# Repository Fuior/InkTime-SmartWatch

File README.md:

# InkTime-SmartWatch

## Project Overview

InkTime-SmartWatch is a compact wearable embedded system built around the Nordic nRF52840 microcontroller, designed for ultra-low-power smartwatch applications using an e-paper display, motion sensing, haptic feedback, battery monitoring and USB-C charging.

The project integrates power management, sensing, display driving and wireless communication into a compact PCB optimized for enclosure integration.

---

# Block Diagram

```text
USB-C Input
   ↓
LiPo Charger
   ↓
LiPo Battery
   ↓
DC/DC Converter
   ↓
nRF52840 MCU
 ├── E-Paper Display (SPI)
 ├── IMU Sensor (I2C)
 ├── Fuel Gauge (I2C)
 ├── Haptic Driver (I2C / GPIO)
 ├── Buttons (GPIO Interrupts)
 ├── SWD Debug Interface
 └── BLE Antenna
```

---

# Bill of Materials (BOM)

| Component         | Part             | Function                       |
| ----------------- | ---------------- | ------------------------------ |
| MCU               | nRF52840-QFAA    | Main microcontroller           |
| Battery Charger   | BQ25180          | LiPo charging                  |
| DC/DC Converter   | RT6150           | Voltage regulation             |
| IMU               | Motion sensor    | Accelerometer / motion sensing |
| Fuel Gauge        | MAX17048         | Battery level measurement      |
| Haptic Driver     | DRV2605          | Vibration motor control        |
| Display Connector | 24-pin FPC       | E-paper connection             |
| USB-C Connector   | Type-C           | Charging and power             |
| ESD Protection    | USBLC6           | USB protection                 |
| Buttons           | Tactile switches | User input                     |
| SWD Header        | TC2030           | Programming/debug              |

---

# Hardware Functional Description

## Microcontroller Core

The central processing unit of the smartwatch is the Nordic nRF52840, a BLE-enabled ARM Cortex-M4 microcontroller selected for:

* low power consumption
* integrated Bluetooth Low Energy
* SPI / I2C / GPIO flexibility
* wearable device suitability

The MCU handles:

* display updates
* sensor acquisition
* battery monitoring
* haptic events
* user input

---

## Power Management

The power subsystem contains:

### LiPo Charger

BQ25180 charger manages battery charging through USB-C input.

Functions:

* battery charging
* input protection
* charging regulation

### DC/DC Converter

RT6150 converts battery voltage to regulated supply rails for MCU and peripherals.

Main outputs:

* 3.3V logic supply
* regulated peripheral rail

---

## Display Subsystem

The smartwatch uses an e-paper display interface.

Advantages:

* ultra low power
* persistent image retention
* sunlight readability

Dedicated E-Paper Driver section generates required voltages.

---

## IMU Sensor

The inertial measurement unit provides motion data:

* acceleration
* movement detection
* orientation sensing

Used for:

* wake-up events
* motion-based interface control

---

## Fuel Gauge

MAX17048 continuously measures battery charge state.

Functions:

* battery voltage monitoring
* charge estimation
* low battery alert

---

## Haptic Feedback

DRV2605 driver controls the vibration motor.

Allows:

* notifications
* tactile feedback
* programmable vibration patterns

---

## USB-C Interface

USB-C connector provides:

* charging input
* power delivery
* ESD protected connection

Protection implemented using USBLC6 device.

---

## Buttons

Three hardware buttons are implemented:

* SW_UP
* SW_INT
* SW_DN

Used for:

* navigation
* selection
* wake-up interrupt

---

# nRF52840 Pin Assignment

| nRF52840 Pin | Connected Module | Interface | Purpose       |
| ------------ | ---------------- | --------- | ------------- |
| P0.13        | Display Clock    | SPI       | Display clock |
| P0.15        | Display Data     | SPI       | Display data  |
| P0.24        | Haptic control   | GPIO      | Motor trigger |
| P0.26        | IMU SDA          | I2C       | Sensor data   |
| P0.27        | IMU SCL          | I2C       | Sensor clock  |
| P1.xx        | Buttons          | GPIO      | User input    |
| SWDIO        | Debug            | SWD       | Programming   |
| SWDCLK       | Debug            | SWD       | Programming   |

---

# Power Consumption Considerations

Estimated current consumption:

* MCU active: ~5 mA
* E-paper refresh: ~20 mA
* IMU active: ~1 mA
* Haptic pulse: ~80 mA

Battery sizing selected for wearable operation with optimized duty cycle.

---

# Mechanical Integration

The mechanical assembly contains:

* PCB
* LiPo battery
* e-paper display
* vibration motor
* enclosure

Placement order:

top to bottom:

Display → Battery → PCB → Case

---

# Design Decisions

Main design goals:

* compact PCB layout
* low power architecture
* short SPI lines to display
* antenna edge placement
* battery direct pad connection

---

# Rendered Images

Project folder contains:

* PCB 3D top render
* PCB 3D side render
* complete assembly top render
* complete assembly side render
* exploded mechanical view

---

# Files Included

## Hardware

* schematic (.sch)
* board (.brd)
* schematic PDF

## Manufacturing

* gerbers.zip
* BOM
* CPL

## Mechanical

* STEP exploded assembly
* STEP PCB 3D
* Fusion360 project

## Images

* PCB renders
* assembly renders

---

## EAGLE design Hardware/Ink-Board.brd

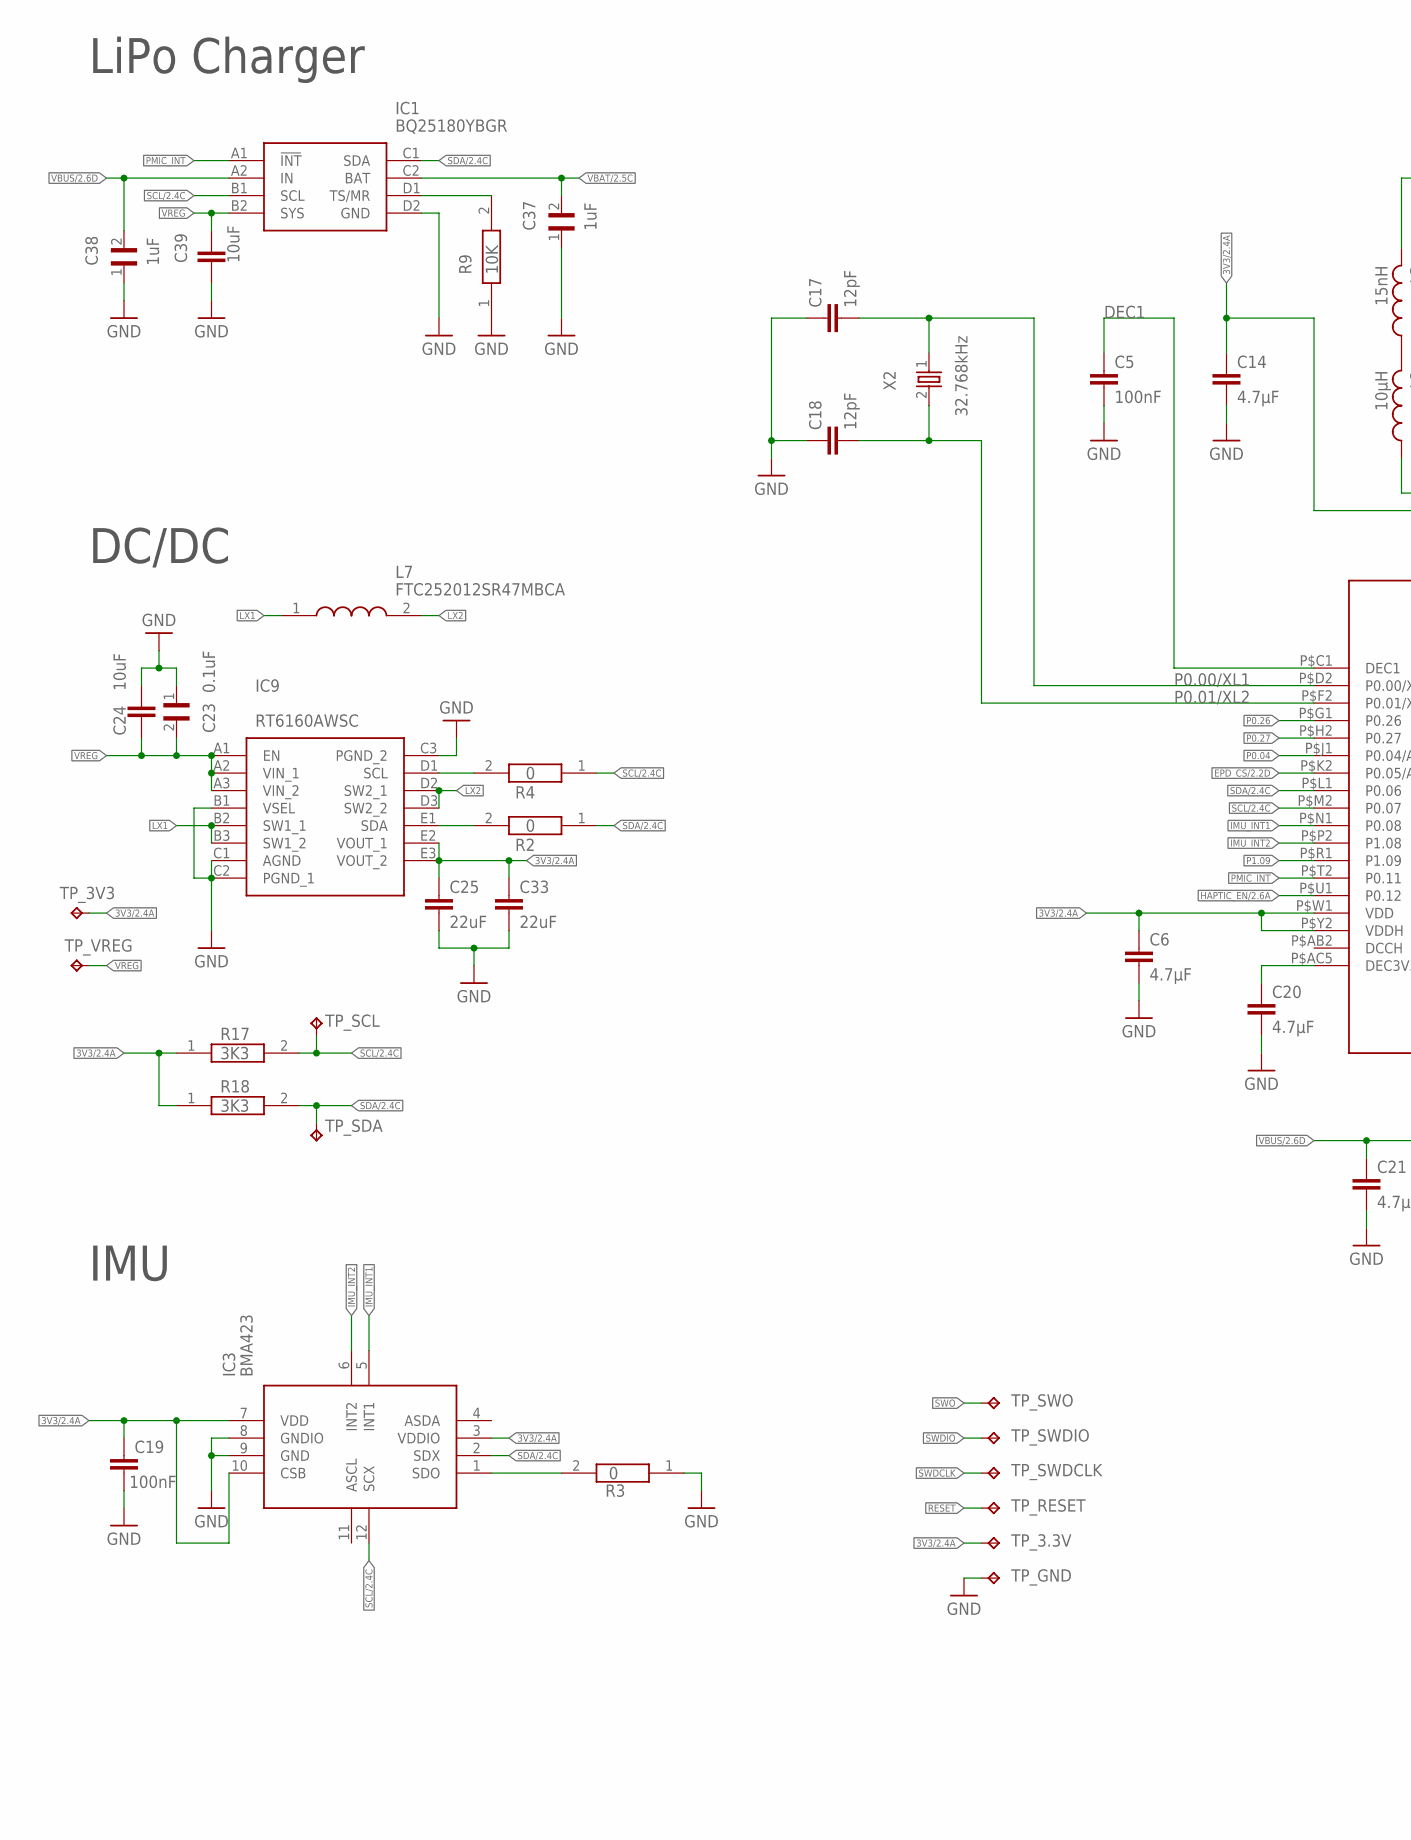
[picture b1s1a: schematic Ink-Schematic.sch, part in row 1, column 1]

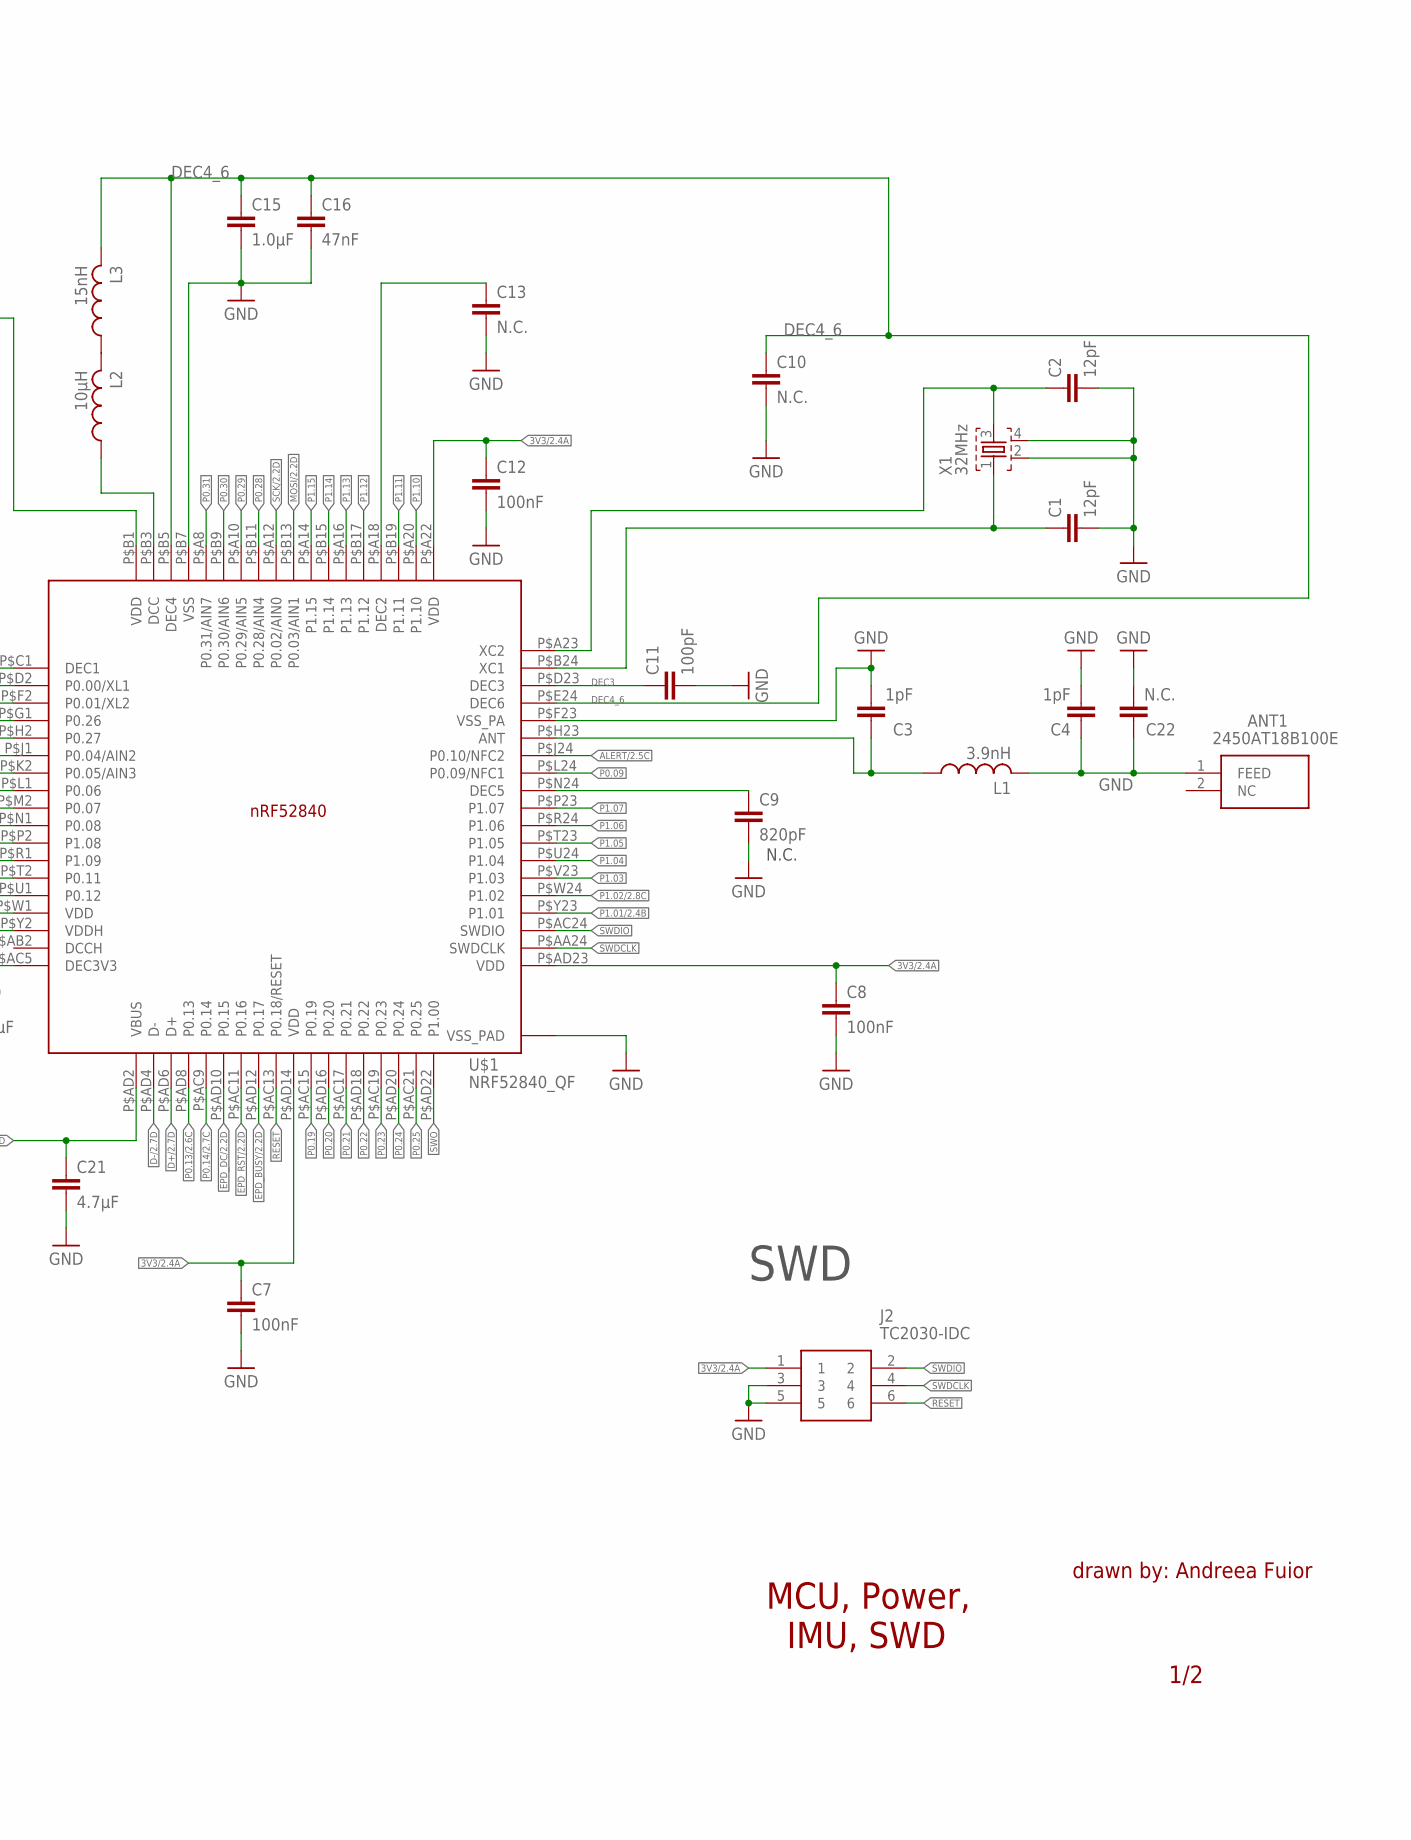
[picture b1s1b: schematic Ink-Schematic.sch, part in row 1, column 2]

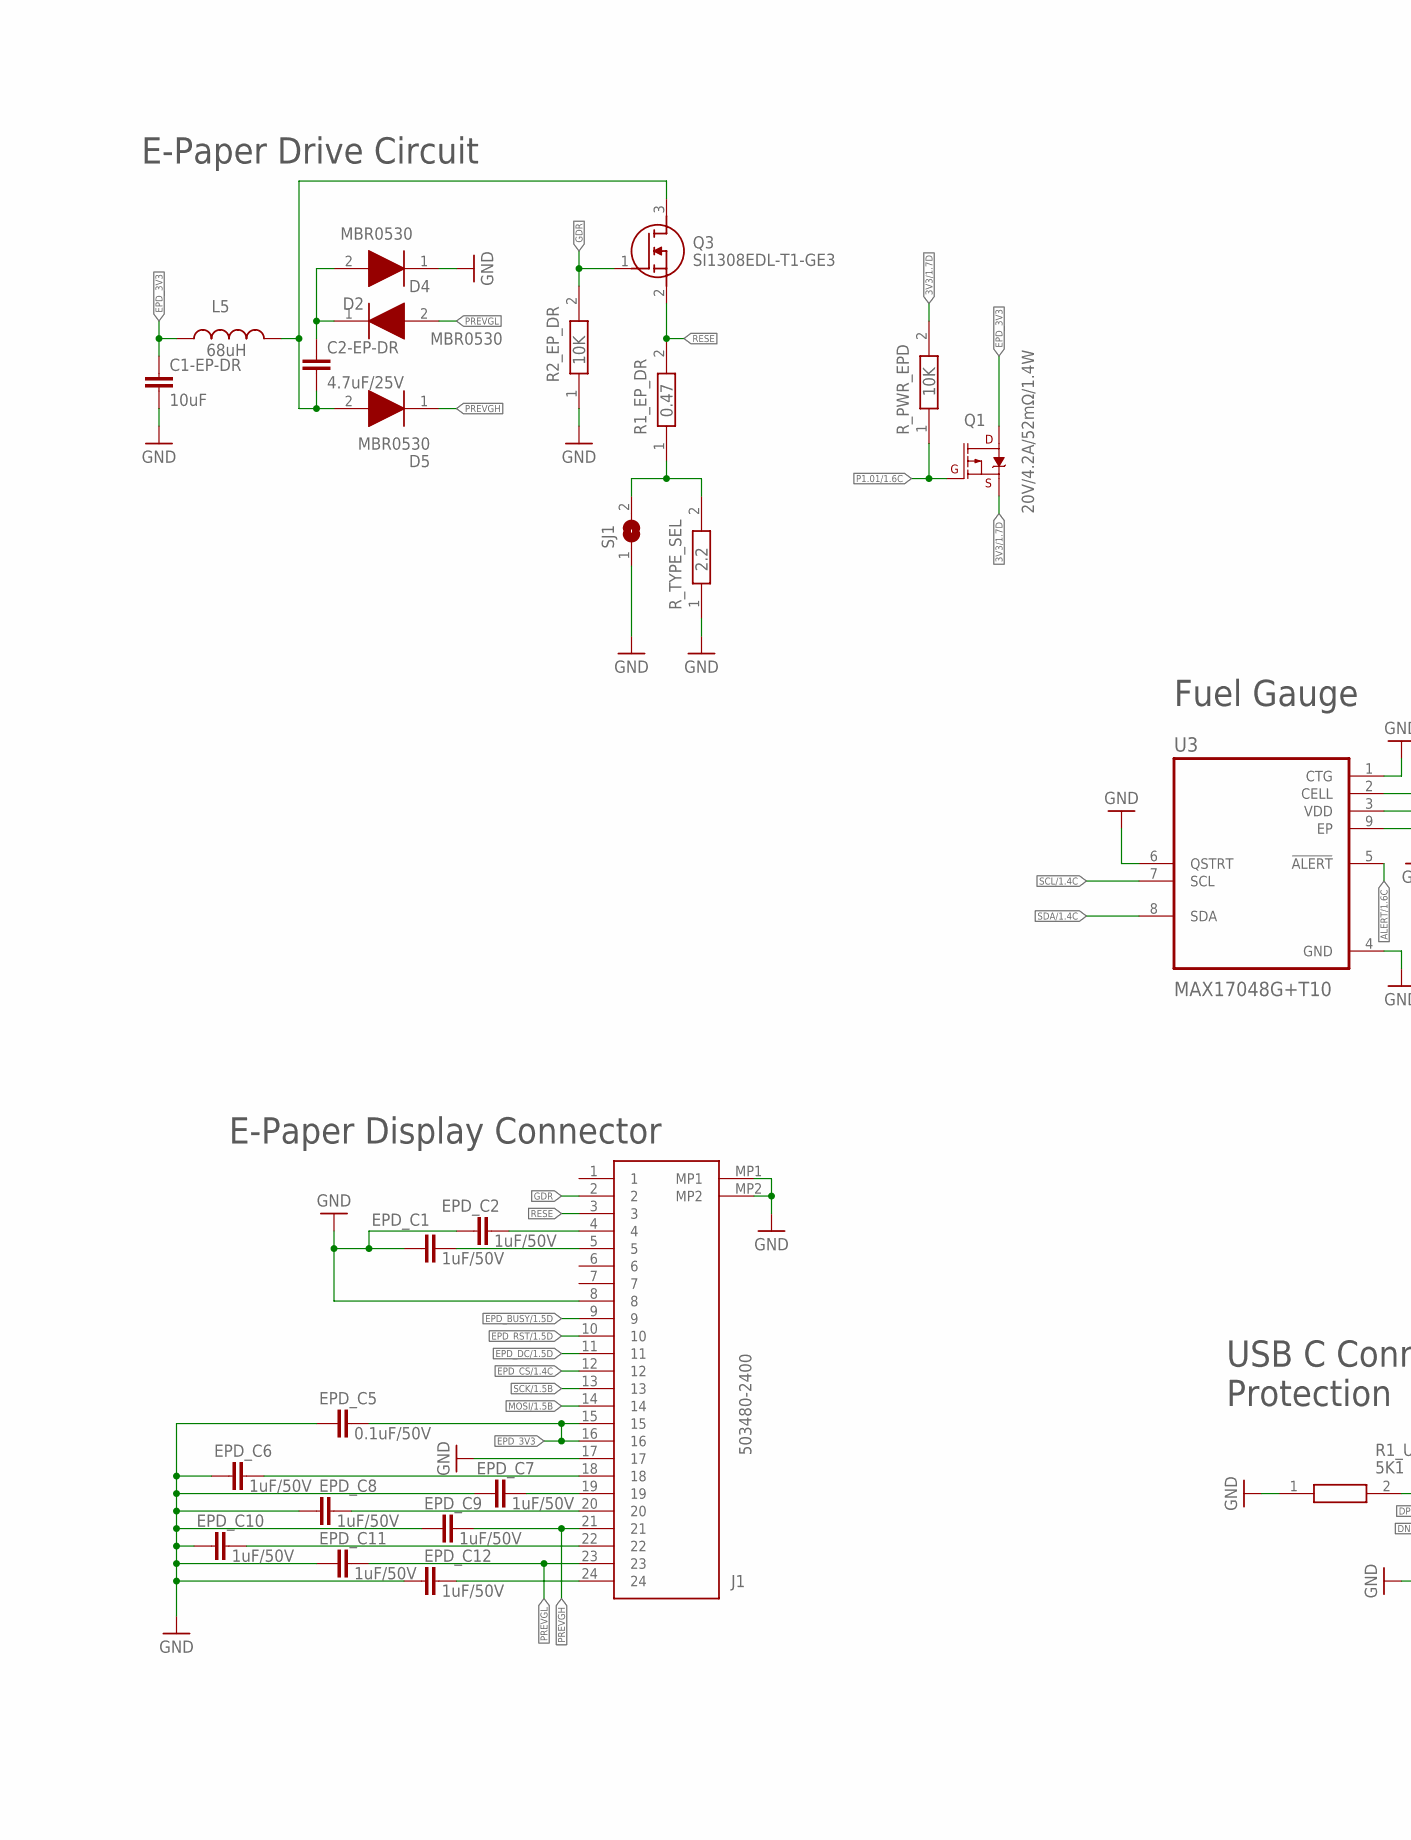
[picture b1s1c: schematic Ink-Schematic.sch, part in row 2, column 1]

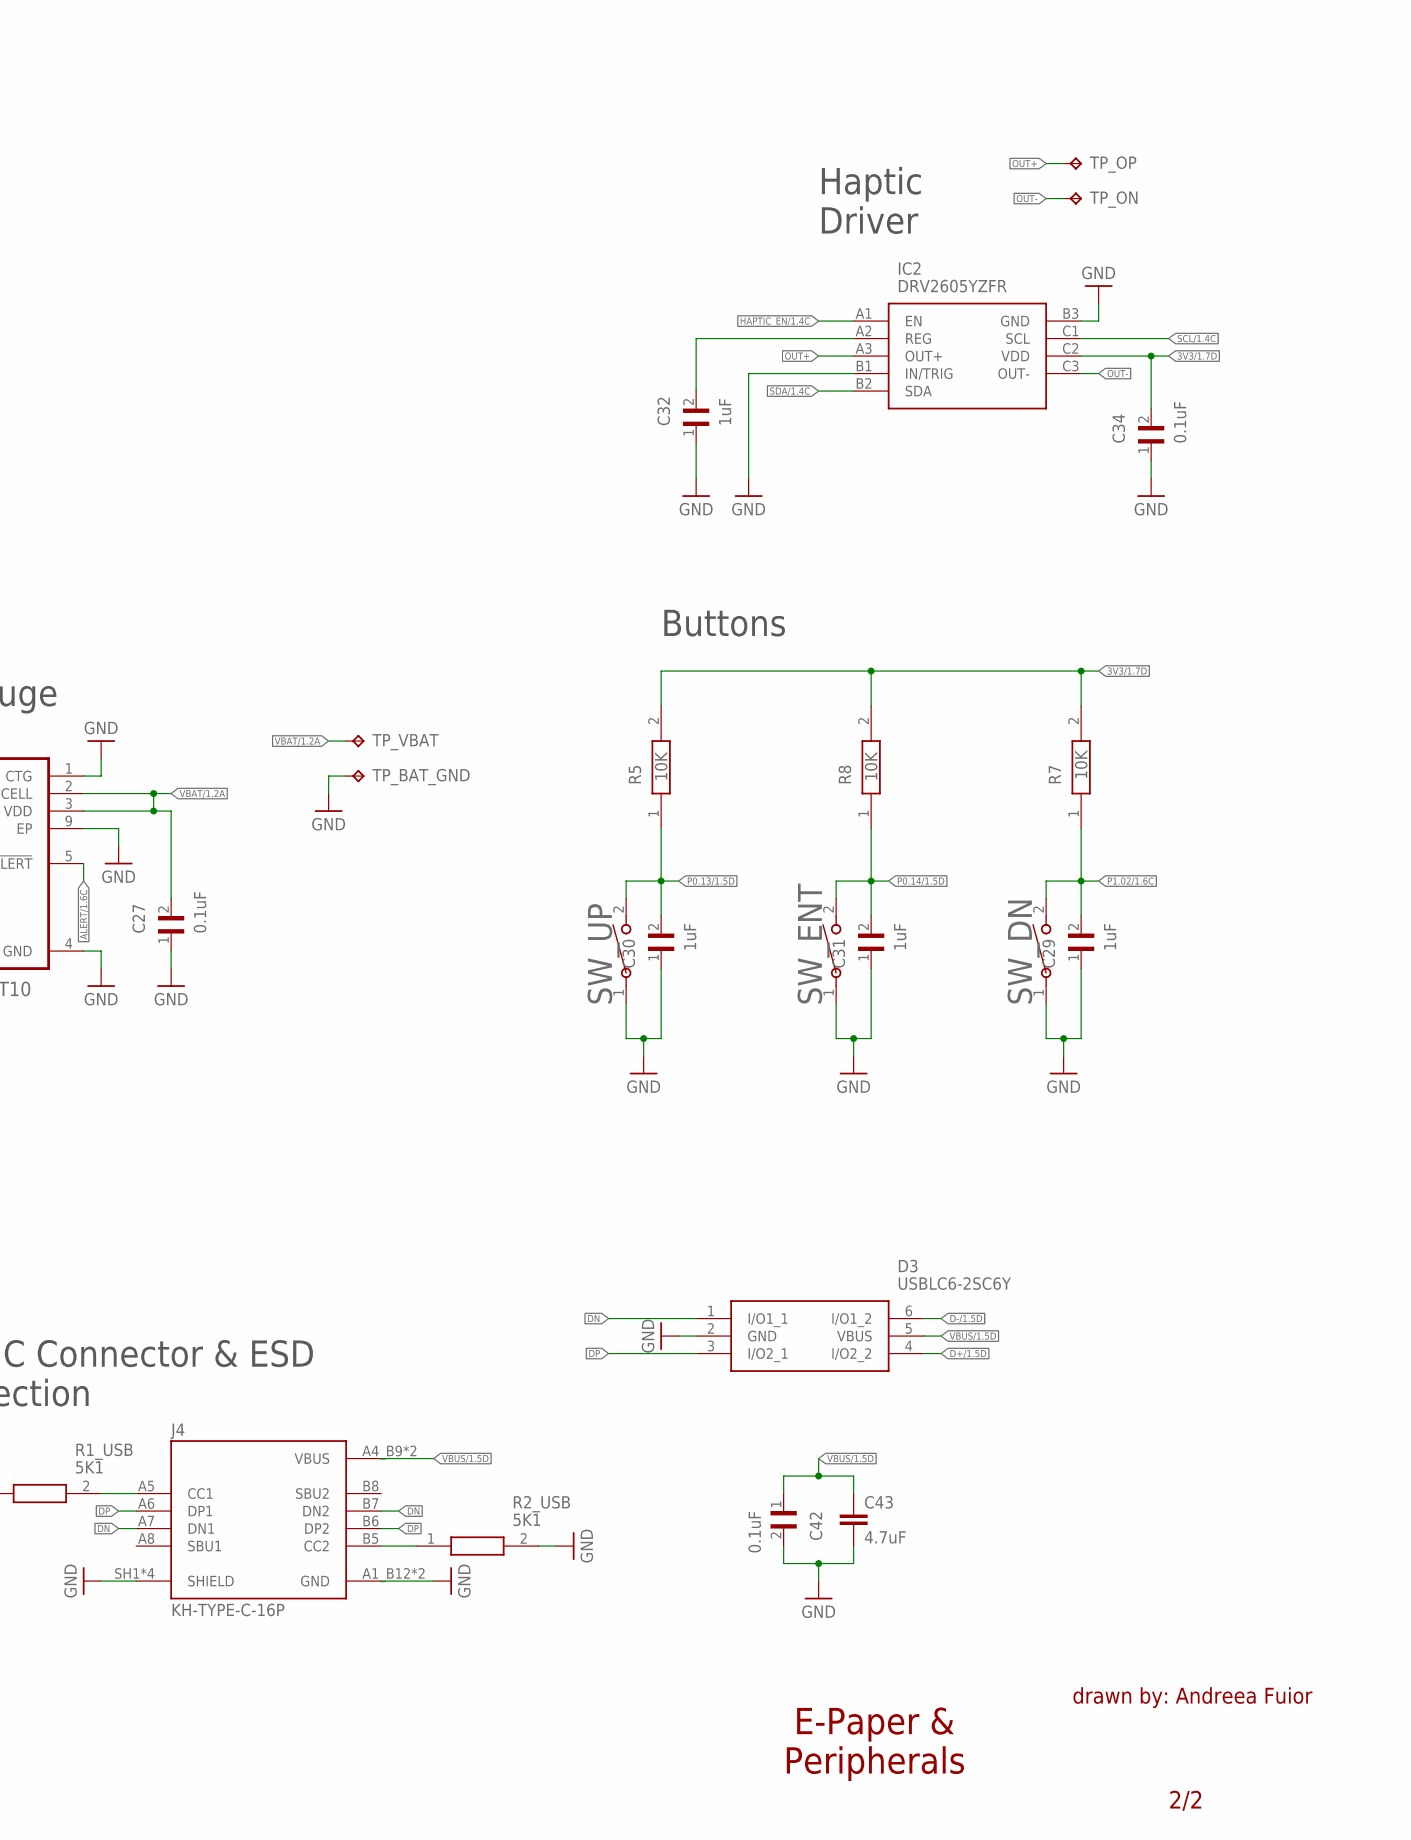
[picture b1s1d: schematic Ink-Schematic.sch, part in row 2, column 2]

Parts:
ANT1: 2450AT18B100E; 2450AT18B100E_ANTC3216X140N
C1, C2, C17, C18: 12pF; NORDIC_NRF_3_RESC0201_L
C1-EP-DR, C24, C39: 10uF; NORDIC_NRF_3_RESC0402_L
C2-EP-DR: 4.7uF/25V; NORDIC_NRF_3_RESC0402_L
C3, C4: 1pF; NORDIC_NRF_3_RESC0201_L
C5, C7, C8, C12, C19: 100nF; NORDIC_NRF_3_RESC0201_L
C6, C14, C20, C21: 4.7μF; NORDIC_NRF_3_RESC0402_L
C9: 820pF; NORDIC_NRF_3_RESC0201_L
C10, C13, C22: N.C.; NORDIC_NRF_3_RESC0201_L
C11: 100pF; NORDIC_NRF_3_RESC0201_L
C15: 1.0μF; NORDIC_NRF_3_RESC0402_L
C16: 47nF; NORDIC_NRF_3_RESC0201_L
C23, C27, C34, C42: 0.1uF; GRM011R60J152KE01L_2_CAPC0201X13N
C25, C33: 22uF; NORDIC_NRF_3_RESC0402_L
C29, C30, C31, C32, C37, C38: 1uF; GRM011R60J152KE01L_2_CAPC0201X13N
C43: 4.7uF; NORDIC_NRF_3_RESC0402_L
D2, D4, D5: MBR0530; ESP32_C6_LIBRARY_5_SOD3716X135N
D3: USBLC6-2SC6Y; ESP32_C6_LIBRARY_3_SOT95P280X145-6N
EPD_C1, EPD_C2, EPD_C6, EPD_C7, EPD_C8, EPD_C9, EPD_C10, EPD_C11, EPD_C12: 1uF/50V; NORDIC_NRF_3_RESC0402_L
EPD_C5: 0.1uF/50V; NORDIC_NRF_3_RESC0402_L
IC1: BQ25180YBGR; BQ25180YBGR_BGA8C40P2X4_100X155X50
IC2: DRV2605YZFR; DRV2605YZFR_BGA9C50P3X3_144X144X62
IC3: BMA423; BMA423_BMA423
IC9: RT6160AWSC; RT6160AWSC_BGA15C40P3X5_140X230X60
J1: 503480-2400; 503480-2400_5034802400
J2: TC2030-IDC; TC2030-IDC_TC2030IDC
J4: KH-TYPE-C-16P; KH-TYPE-C-16P_KINGHELM_KH-TYPE-C-16P
L1: 3.9nH; NORDIC_NRF_2_RESC0402_L
L2: 10μH; NORDIC_NRF_2_RESC0402_L
L3: 15nH; NORDIC_NRF_2_RESC0402_L
L5: 68uH; NORDIC_NRF_2_RESC0402_L
L7: FTC252012SR47MBCA; MLP2016SR47MT0S1_INDC2016X100N
Q1: 20V/4.2A/52mΩ/1.4W; ESP32_C6_LIBRARY_4_ESP32_C6_LIBRARY_4_ESP32_C6_LIBRARY_4_ES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
Q3: SI1308EDL-T1-GE3; ESP32_C6_LIBRARY_6_SOT65P210X110-3N
R1_EP_DR: 0.47; CPF0201D7K68C1_0201
R1_USB, R2_USB: 5K1; CPF0201D7K68C1_0201
R2, R3, R4: 0; CPF0201D7K68C1_0201
R2_EP_DR, R5, R7, R8, R9: 10K; CPF0201D7K68C1_0201
R17, R18: 3K3; CPF0201D7K68C1_0201
R_PWR_EPD: 10K; CPF0201D7K68C1_0201
R_TYPE_SEL: 2.2; CPF0201D7K68C1_0201
SJ1: ESP32_C6_LIBRARY_7_JUMPER_SJ
SW_DN: 2025-10-22_07-23-44_LIBRARY_EVP-AKE31ASW_EVP-AKE3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; 2025-10-22_07-23-44_LIBRARY_SW_EVP-AKE31A_PAN
SW_ENT: 2025-10-22_07-23-44_LIBRARY_EVP-AKE31ASW_EVP-AKE3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; 2025-10-22_07-23-44_LIBRARY_SW_EVP-AKE31A_PAN
SW_UP: 2025-10-22_07-23-44_LIBRARY_EVP-AKE31ASW_EVP-AKE3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; 2025-10-22_07-23-44_LIBRARY_SW_EVP-AKE31A_PAN
TP_3.3V, TP_3V3: HECTOR_WATCH_1_TPTP20R; HECTOR_WATCH_1_TP20R
TP_BAT_GND: HECTOR_WATCH_1_TPTP20R; HECTOR_WATCH_1_TP20R
TP_GND: HECTOR_WATCH_1_TPTP20R; HECTOR_WATCH_1_TP20R
TP_ON: HECTOR_WATCH_1_TPTP20R; HECTOR_WATCH_1_TP20R
TP_OP: HECTOR_WATCH_1_TPTP20R; HECTOR_WATCH_1_TP20R
TP_RESET: HECTOR_WATCH_1_TPTP20R; HECTOR_WATCH_1_TP20R
TP_SCL: HECTOR_WATCH_1_TPTP20R; HECTOR_WATCH_1_TP20R
TP_SDA: HECTOR_WATCH_1_TPTP20R; HECTOR_WATCH_1_TP20R
TP_SWDCLK: HECTOR_WATCH_1_TPTP20R; HECTOR_WATCH_1_TP20R
TP_SWDIO: HECTOR_WATCH_1_TPTP20R; HECTOR_WATCH_1_TP20R
TP_SWO: HECTOR_WATCH_1_TPTP20R; HECTOR_WATCH_1_TP20R
TP_VBAT: HECTOR_WATCH_1_TPTP20R; HECTOR_WATCH_1_TP20R
TP_VREG: HECTOR_WATCH_1_TPTP20R; HECTOR_WATCH_1_TP20R
U3: MAX17048G+T10; ESP32_C6_LIBRARY_SON50P200X200X80-9N
U$1: NRF52840_QF; NORDIC_NRF_4_AQFN50P700X700X85_HS-74N
X1: 32MHz; NORDIC_NRF_BT-XTAL_2016_N
X2: 32.768kHz; NORDIC_NRF_1_XTAL_3215_N

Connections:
3V3/1.7D: C34.2, IC2.C2 (VDD), Q1.2 (S), R5.2, R7.2, R8.2, R_PWR_EPD.2
3V3/2.4A: C6.1, C7.1, C8.1, C12.1, C14.1, C19.1, C25.1, C33.1, IC3.3 (VDDIO), IC3.7 (VDD), IC3.10 (CSB), IC9.E2 (VOUT_1), IC9.E3 (VOUT_2), J2.1, R17.1, R18.1, TP_3.3V.TP, TP_3V3.TP, U$1.P$A22 (VDD), U$1.P$AD14 (VDD), U$1.P$AD23 (VDD), U$1.P$B1 (VDD), U$1.P$W1 (VDD), U$1.P$Y2 (VDDH)
ALERT/1.6C: U3.5 (!ALERT)
ALERT/2.5C: U$1.P$J24 (P0.10/NFC2)
D+/1.5D: D3.4 (I/O2_2)
D+/2.7D: U$1.P$AD6 (D+)
D-/1.5D: D3.6 (I/O1_2)
D-/2.7D: U$1.P$AD4 (D-)
DEC1: C5.1, U$1.P$C1 (DEC1)
DEC3: C11.1, U$1.P$D23 (DEC3)
DEC4_6: C10.1, C15.1, C16.1, L3.2, U$1.P$B5 (DEC4), U$1.P$E24 (DEC6)
DN: D3.1 (I/O1_1), J4.A7 (DN1), J4.B7 (DN2)
DP: D3.3 (I/O2_1), J4.A6 (DP1), J4.B6 (DP2)
EPD_3V3: C1-EP-DR.1, EPD_C5.1, J1.15, J1.16, L5.1, Q1.3 (D)
EPD_BUSY/1.5D: J1.9
EPD_BUSY/2.2D: U$1.P$AD12 (P0.17)
EPD_CS/1.4C: J1.12
EPD_CS/2.2D: U$1.P$K2 (P0.05/AIN3)
EPD_DC/1.5D: J1.11
EPD_DC/2.2D: U$1.P$AD10 (P0.15)
EPD_RST/1.5D: J1.10
EPD_RST/2.2D: U$1.P$AC11 (P0.16)
GDR: J1.2, Q3.1 (G), R2_EP_DR.2
GND: ANT1.1 (FEED), C1.2, C1-EP-DR.2, C2.2, C3.2, C4.1, C4.2, C5.2, C6.2, C7.2, C8.2, C9.2, C10.2, C11.2, C12.2, C13.2, C14.2, C15.2, C16.2, C17.1, C18.1, C19.2, C20.2, C21.2, C22.1, C22.2, C23.1, C24.2, C25.2, C27.1, C29.1, C30.1, C31.1, C32.1, C33.2, C34.1, C37.1, C38.1, C39.2, C42.2, C43.2, D3.2 (GND), D4.1 (K), EPD_C1.2, EPD_C2.2, EPD_C5.2, EPD_C6.2, EPD_C7.2, EPD_C8.2, EPD_C9.2, EPD_C10.2, EPD_C11.2, EPD_C12.2, IC1.D2 (GND), IC2.B1 (IN/TRIG), IC2.B3 (GND), IC3.8 (GNDIO), IC3.9 (GND), IC9.B1 (VSEL), IC9.C1 (AGND), IC9.C2 (PGND_1), IC9.C3 (PGND_2), J1.8, J1.17, J1.MP1, J1.MP2, J2.3, J2.5, J4.A1_B12 (GND), J4.A12_B1 (GND), J4.SH1 (SHIELD), J4.SH2 (SHIELD), J4.SH3 (SHIELD), J4.SH4 (SHIELD), L1.2, R1_USB.1, R2_EP_DR.1, R2_USB.2, R3.1, R9.1, R_TYPE_SEL.1, SJ1.1, SW_DN.1, SW_ENT.1, SW_UP.1, TP_BAT_GND.TP, TP_GND.TP, U3.1 (CTG), U3.4 (GND), U3.6 (QSTRT), U3.9 (EP), U$1.P$74 (VSS_PAD), U$1.P$75 (VSS_PAD), U$1.P$76 (VSS_PAD), U$1.P$77 (VSS_PAD), U$1.P$78 (VSS_PAD), U$1.P$79 (VSS_PAD), U$1.P$80 (VSS_PAD), U$1.P$81 (VSS_PAD), U$1.P$82 (VSS_PAD), U$1.P$83 (VSS_PAD), U$1.P$84 (VSS_PAD), U$1.P$85 (VSS_PAD), U$1.P$86 (VSS_PAD), U$1.P$87 (VSS_PAD), U$1.P$88 (VSS_PAD), U$1.P$89 (VSS_PAD), U$1.P$90 (VSS_PAD), U$1.P$B7 (VSS), U$1.P$F23 (VSS_PA), X1.2, X1.4
HAPTIC_EN/1.4C: IC2.A1 (EN)
HAPTIC_EN/2.6A: U$1.P$U1 (P0.12)
IMU_INT1: IC3.5 (INT1), U$1.P$N1 (P0.08)
IMU_INT2: IC3.6 (INT2), U$1.P$P2 (P1.08)
LX1: IC9.B2 (SW1_1), IC9.B3 (SW1_2), L7.1
LX2: IC9.D2 (SW2_1), IC9.D3 (SW2_2), L7.2
MOSI/1.5B: J1.14
MOSI/2.2D: U$1.P$B13 (P0.03/AIN1)
unnamed: C9.1, U$1.P$N24 (DEC5)
unnamed: C3.1, L1.1, U$1.P$H23 (ANT)
unnamed: C1.1, U$1.P$B24 (XC1), X1.1
unnamed: C2.1, U$1.P$A23 (XC2), X1.3
unnamed: C13.1, U$1.P$A18 (DEC2)
unnamed: L2.1, U$1.P$B3 (DCC)
unnamed: L2.2, L3.1
unnamed: C20.1, U$1.P$AC5 (DEC3V3)
unnamed: C2-EP-DR.2, D5.2 (A), L5.2, Q3.3 (D)
unnamed: IC9.D1 (SCL), R4.2
unnamed: IC1.D1 (TS/MR), R9.2
unnamed: C2-EP-DR.1, D2.1 (K), D4.2 (A)
unnamed: IC9.E1 (SDA), R2.2
unnamed: EPD_C2.1, J1.4
unnamed: R1_EP_DR.1, R_TYPE_SEL.2, SJ1.2
unnamed: IC3.1 (SDO), R3.2
unnamed: EPD_C6.1, J1.18
unnamed: EPD_C7.1, J1.19
unnamed: EPD_C8.1, J1.20
unnamed: EPD_C1.1, J1.5
unnamed: EPD_C10.1, J1.22
unnamed: EPD_C12.1, J1.24
unnamed: C32.2, IC2.A2 (REG)
unnamed: J4.B5 (CC2), R2_USB.1
unnamed: J4.A5 (CC1), R1_USB.2
OUT+: IC2.A3 (OUT+), TP_OP.TP
OUT-: IC2.C3 (OUT-), TP_ON.TP
P0.00/XL1: C17.2, U$1.P$D2 (P0.00/XL1), X2.1
P0.01/XL2: C18.2, U$1.P$F2 (P0.01/XL2), X2.2
P0.04: U$1.P$J1 (P0.04/AIN2)
P0.09: U$1.P$L24 (P0.09/NFC1)
P0.13/1.5D: C30.2, R5.1, SW_UP.2
P0.13/2.6C: U$1.P$AD8 (P0.13)
P0.14/1.5D: C31.2, R8.1, SW_ENT.2
P0.14/2.7C: U$1.P$AC9 (P0.14)
P0.19: U$1.P$AC15 (P0.19)
P0.20: U$1.P$AD16 (P0.20)
P0.21: U$1.P$AC17 (P0.21)
P0.22: U$1.P$AD18 (P0.22)
P0.23: U$1.P$AC19 (P0.23)
P0.24: U$1.P$AD20 (P0.24)
P0.25: U$1.P$AC21 (P0.25)
P0.26: U$1.P$G1 (P0.26)
P0.27: U$1.P$H2 (P0.27)
P0.28: U$1.P$B11 (P0.28/AIN4)
P0.29: U$1.P$A10 (P0.29/AIN5)
P0.30: U$1.P$B9 (P0.30/AIN6)
P0.31: U$1.P$A8 (P0.31/AIN7)
P1.01/1.6C: Q1.1 (G), R_PWR_EPD.1
P1.01/2.4B: U$1.P$Y23 (P1.01)
P1.02/1.6C: C29.2, R7.1, SW_DN.2
P1.02/2.8C: U$1.P$W24 (P1.02)
P1.03: U$1.P$V23 (P1.03)
P1.04: U$1.P$U24 (P1.04)
P1.05: U$1.P$T23 (P1.05)
P1.06: U$1.P$R24 (P1.06)
P1.07: U$1.P$P23 (P1.07)
P1.09: U$1.P$R1 (P1.09)
P1.10: U$1.P$A20 (P1.10)
P1.11: U$1.P$B19 (P1.11)
P1.12: U$1.P$B17 (P1.12)
P1.13: U$1.P$A16 (P1.13)
P1.14: U$1.P$B15 (P1.14)
P1.15: U$1.P$A14 (P1.15)
PMIC_INT: IC1.A1 (!INT), U$1.P$T2 (P0.11)
PREVGH: D5.1 (K), EPD_C9.1, J1.21
PREVGL: D2.2 (A), EPD_C11.1, J1.23
RESE: J1.3, Q3.2 (S), R1_EP_DR.2
RESET: J2.6, TP_RESET.TP, U$1.P$AC13 (P0.18/RESET)
SCK/1.5B: J1.13
SCK/2.2D: U$1.P$A12 (P0.02/AIN0)
SCL/1.4C: IC2.C1 (SCL), U3.7 (SCL)
SCL/2.4C: IC1.B1 (SCL), IC3.12 (SCX), R4.1, R17.2, TP_SCL.TP, U$1.P$M2 (P0.07)
SDA/1.4C: IC2.B2 (SDA), U3.8 (SDA)
SDA/2.4C: IC1.C1 (SDA), IC3.2 (SDX), R2.1, R18.2, TP_SDA.TP, U$1.P$L1 (P0.06)
SWDCLK: J2.4, TP_SWDCLK.TP, U$1.P$AA24 (SWDCLK)
SWDIO: J2.2, TP_SWDIO.TP, U$1.P$AC24 (SWDIO)
SWO: TP_SWO.TP, U$1.P$AD22 (P1.00)
VBAT/1.2A: C27.2, TP_VBAT.TP, U3.2 (CELL), U3.3 (VDD)
VBAT/2.5C: C37.2, IC1.C2 (BAT)
VBUS/1.5D: C42.1, C43.1, D3.5 (VBUS), J4.A4_B9 (VBUS), J4.A9_B4 (VBUS)
VBUS/2.6D: C21.1, C38.2, IC1.A2 (IN), U$1.P$AD2 (VBUS)
VREG: C23.2, C24.1, C39.1, IC1.B2 (SYS), IC9.A1 (EN), IC9.A2 (VIN_1), IC9.A3 (VIN_2), TP_VREG.TP

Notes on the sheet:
SWD
LiPo Charger
DC/DC
IMU
E-Paper Drive Circuit
E-Paper Display Connector
Haptic Driver
Buttons
Fuel Gauge
USB C Connector & ESD Protection
MCU, Power, IMU, SWD
drawn by: Andreea Fuior
E-Paper & Peripherals
1/2
2/2
N.C.

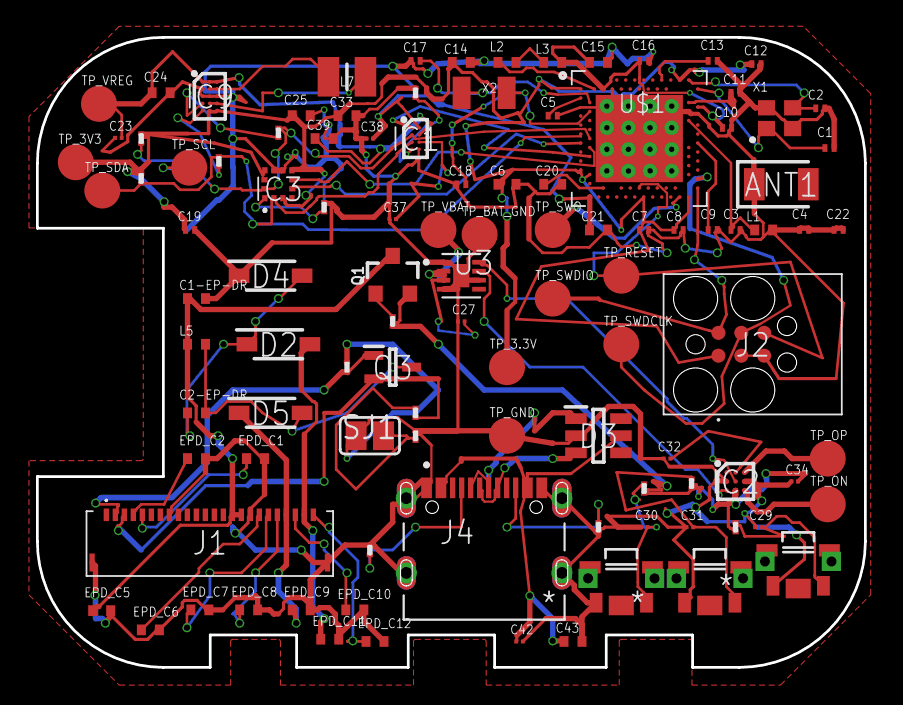
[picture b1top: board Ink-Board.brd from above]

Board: 2 copper layers, 46.0 x 35.0 mm, 105 parts (0 on the bottom side), 64 nets.

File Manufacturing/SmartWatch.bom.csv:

Reference Designators;Quantity;Description;Package;Value;Manufacturer;Manufacturer Part Number;Vendor;Vendor Part Number;Top/Bottom;
;1;Board;Board;;;;;;;
ANT1;1;Antennas 2.45GHz ANTENNA;2450AT18B100E_ANTC3216X140N;2450AT18B100E;;;;;Top;
C1, C2, C17, C18;4;Generic chip capacitor;NORDIC_NRF_3_RESC0201_L;12pF;;;;;Top;
C1-EP-DR, C24, C39;3;Generic chip capacitor;NORDIC_NRF_3_RESC0402_L;10uF;;;;;Top;
C2-EP-DR;1;Generic chip capacitor;NORDIC_NRF_3_RESC0402_L;4.7uF/25V;;;;;Top;
C3, C4;2;Generic chip capacitor;NORDIC_NRF_3_RESC0201_L;1pF;;;;;Top;
C5, C7, C8, C12, C19;5;Generic chip capacitor;NORDIC_NRF_3_RESC0201_L;100nF;;;;;Top;
C6, C14, C20, C21;4;Generic chip capacitor;NORDIC_NRF_3_RESC0402_L;4.7μF;;;;;Top;
C9;1;Generic chip capacitor;NORDIC_NRF_3_RESC0201_L;820pF;;;;;Top;
C10, C13, C22;3;Generic chip capacitor;NORDIC_NRF_3_RESC0201_L;N.C.;;;;;Top;
C11;1;Generic chip capacitor;NORDIC_NRF_3_RESC0201_L;100pF;;;;;Top;
C15;1;Generic chip capacitor;NORDIC_NRF_3_RESC0402_L;1.0μF;;;;;Top;
C16;1;Generic chip capacitor;NORDIC_NRF_3_RESC0201_L;47nF;;;;;Top;
C23, C27, C34, C42;4;Check availability;CAPC0201X13N;0.1uF;;;;;Top;
C25, C33;2;Generic chip capacitor;NORDIC_NRF_3_RESC0402_L;22uF;;;;;Top;
C29, C30, C31, C32, C37, C38;6;Check availability;CAPC0201X13N;1uF;;;;;Top;
C43;1;Generic chip capacitor;NORDIC_NRF_3_RESC0402_L;4.7uF;;;;;Top;
D2, D4, D5;3;ON SEMICONDUCTOR - MBR0530 - DIODE, SCHOTTKY, 0.5A, 30V, SOD-123;SOD3716X135N;MBR0530;;;;;Top;
D3;1;Low Cap. ESD Protection Auto SOT-23-6 STMicroelectronics USBLC6-2SC6Y, Dual Uni-Directional TVS Diode Array, 6-Pin SOT-23;SOT95P280X145-6N;USBLC6-2SC6Y;;;;;Top;
EPD_C1, EPD_C2, EPD_C6, EPD_C7, EPD_C8, EPD_C9, EPD_C10, EPD_C11, EPD_C12;9;Generic chip capacitor;NORDIC_NRF_3_RESC0402_L;1uF/50V;;;;;Top;
EPD_C5;1;Generic chip capacitor;NORDIC_NRF_3_RESC0402_L;0.1uF/50V;;;;;Top;
IC1;1;Charger IC Lithium Ion/Polymer, Lithium Iron Phosphate 8-DSBGA (1.6x1.1);BQ25180YBGR_BGA8C40P2X4_100X155X50;BQ25180YBGR;;;;;Top;
IC2;1;Haptic Driver for ERM/LRA with Built-In Library and Smart Loop Architecture;DRV2605YZFR_BGA9C50P3X3_144X144X62;DRV2605YZFR;;;;;Top;
IC3;1;Accelerometers Triaxial low-g 12bit Acceleration Sensor;BMA423_BMA423; BMA423;;;;;Top;
IC9;1;Buck-Boost Regulator Positive Output Step-Up/Step-Down I2C DC-DC Controller IC 15-WL-CSP (BSC) (1.4x2.3);RT6160AWSC_BGA15C40P3X5_140X230X60;RT6160AWSC;;;;;Top;
J1;1;FFC & FPC Connectors 0.5mm FPC RA SMT Dual Contact 24Ckt;503480-2400_5034802400;503480-2400;;;;;Top;
J2;1;CABLE ADAPTER 6 POS;TC2030-IDC_TC2030IDC;TC2030-IDC;;;;;Top;
J4;1;Check availability;KINGHELM_KH-TYPE-C-16P;KH-TYPE-C-16P;;;;;Top;
L1;1;Generic chip inductor;NORDIC_NRF_2_RESC0402_L;3.9nH;;;;;Top;
L2;1;Generic chip inductor;NORDIC_NRF_2_RESC0402_L; 10μH;;;;;Top;
L3;1;Generic chip inductor;NORDIC_NRF_2_RESC0402_L;15nH;;;;;Top;
L5;1;Generic chip inductor;NORDIC_NRF_2_RESC0402_L;68uH;;;;;Top;
L7;1;SMD / SMT Inductors (Coils), L=0.47?H, L x W x T :;MLP2016SR47MT0S1_INDC2016X100N;FTC252012SR47MBCA;;;;;Top;
Q1;1;P-channel MOSFETs;ESP32_WROVER_SPARKFUN-DISCRETESEMI_SOT23-3;20V/4.2A/52mΩ/1.4W;;;;;Top;
Q3;1;MOSFET N-Ch 30V 1.5A TrenchFET SC70 Vishay Si1308EDL-T1-GE3 N-channel MOSFET Transistor, 1.5 A, 30 V, 3-Pin SC-70;SOT65P210X110-3N;SI1308EDL-T1-GE3;;;;;Top;
R_PWR_EPD, R5, R7, R8;4;7.68k 0201 Thin Film Surface Mount Fixed Resistor +/-0.5% 0.031W CPF0201D7K68C1;CPF0201D7K68C1_0201;10K;;;;;Top;
R_TYPE_SEL;1;7.68k 0201 Thin Film Surface Mount Fixed Resistor +/-0.5% 0.031W CPF0201D7K68C1;CPF0201D7K68C1_0201;2.2;;;;;Top;
R1_EP_DR;1;7.68k 0201 Thin Film Surface Mount Fixed Resistor +/-0.5% 0.031W CPF0201D7K68C1;CPF0201D7K68C1_0201; 0.47;;;;;Top;
R1_USB, R2_USB;2;7.68k 0201 Thin Film Surface Mount Fixed Resistor +/-0.5% 0.031W CPF0201D7K68C1;CPF0201D7K68C1_0201;5K1;;;;;Top;
R2, R4;2;7.68k 0201 Thin Film Surface Mount Fixed Resistor +/-0.5% 0.031W CPF0201D7K68C1;CPF0201D7K68C1_0201;0;;;;;Top;
R2_EP_DR, R9;2;7.68k 0201 Thin Film Surface Mount Fixed Resistor +/-0.5% 0.031W CPF0201D7K68C1;CPF0201D7K68C1_0201; 10K;;;;;Top;
R3;1;7.68k 0201 Thin Film Surface Mount Fixed Resistor +/-0.5% 0.031W CPF0201D7K68C1;CPF0201D7K68C1_0201; 0;;;;;Top;
R17, R18;2;7.68k 0201 Thin Film Surface Mount Fixed Resistor +/-0.5% 0.031W CPF0201D7K68C1;CPF0201D7K68C1_0201; 3K3;;;;;Top;
SJ1;1;SMD solder JUMPER;JUMPER_SJ;;;;;;Top;
SW_DN, SW_ENT, SW_UP;3;;SW_EVP-AKE31A_PAN;2025-10-22_07-23-44_LIBRARY_EVP-AKE31ASW_EVP-AKE31A_PAN;;;;;Top;
TP_3.3V, TP_3V3, TP_BAT_GND, TP_GND, TP_ON, TP_OP, TP_RESET, TP_SCL, TP_SDA, TP_SWDCLK, TP_SWDIO, TP_SWO, TP_VBAT, TP_VREG;14;Test pad;HECTOR_WATCH_1_TP20R;HECTOR_WATCH_1_TPTP20R;;;;;Top;
U$1;1;nRF52840;NORDIC_NRF_4_AQFN50P700X700X85_HS-74N;NRF52840_QF;;;;;Top;
U3;1;Check availability;SON50P200X200X80-9N;MAX17048G+T10;;;;;Top;
X1;1;;NORDIC_NRF_BT-XTAL_2016_N;32MHz;;;;;Top;
X2;1;;NORDIC_NRF_1_XTAL_3215_N;32.768kHz;;;;;Top;

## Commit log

2026-04-10 First steps of the project
2026-04-22 Updating the project
2026-04-22 Adding Images

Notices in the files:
parts and their libraries:
COPYRIGHT: Copyright (C) 2025 Ultra Librarian. All rights reserved.
